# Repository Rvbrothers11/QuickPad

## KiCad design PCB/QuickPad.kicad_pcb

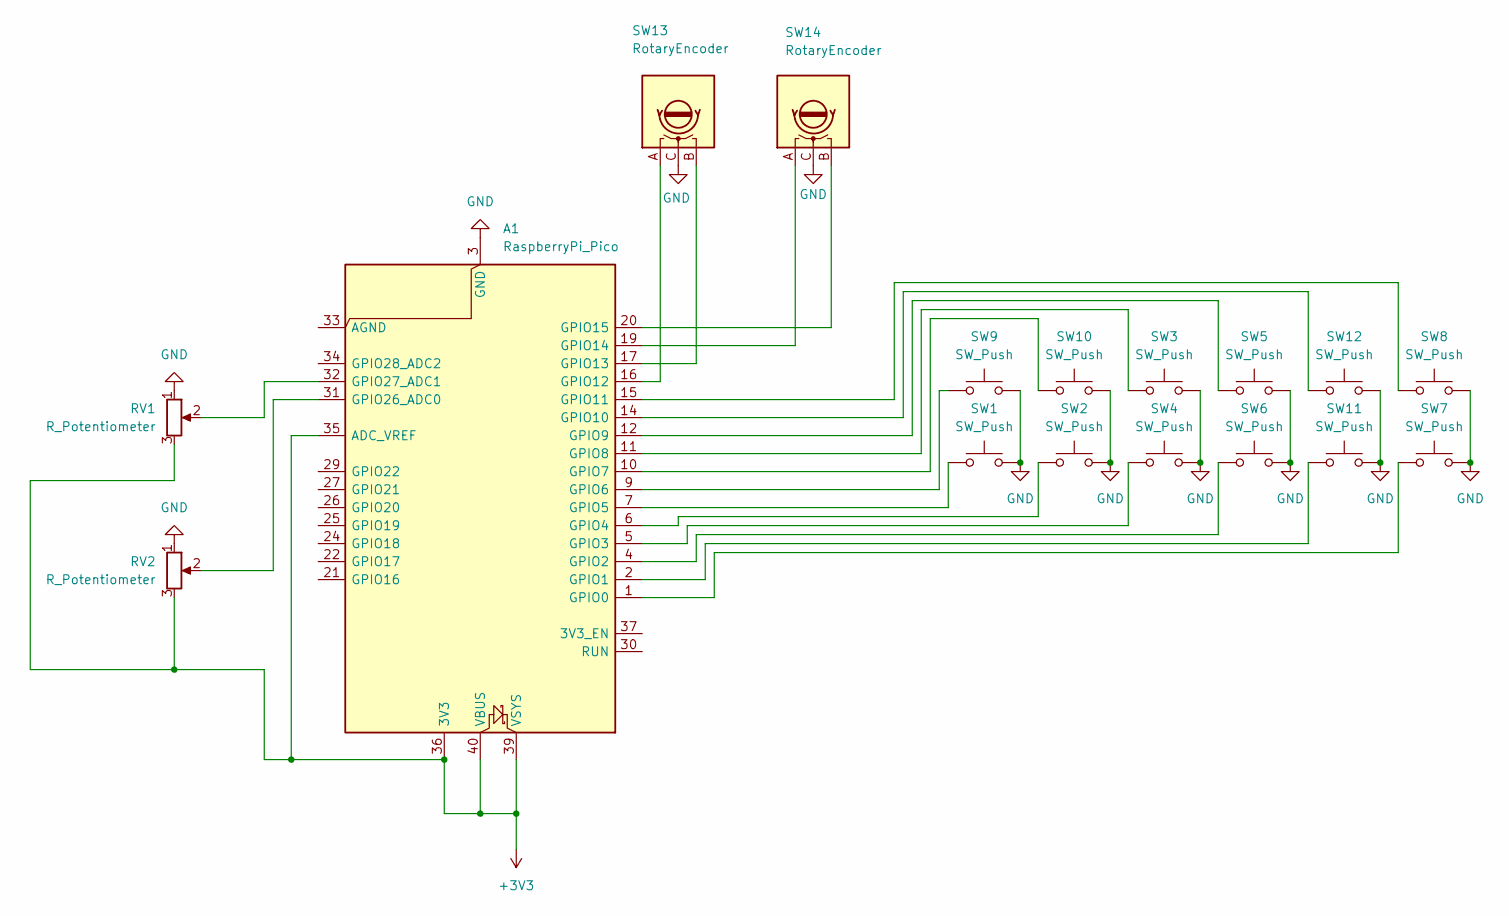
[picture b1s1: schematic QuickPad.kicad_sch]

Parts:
A1: RaspberryPi_Pico; RaspberryPi_Pico_SMD
RV1, RV2: R_Potentiometer; Potentiometer_Bourns_PTA2043_Single_Slide
SW1, SW2, SW3, SW4, SW5, SW6, SW7, SW8, SW9, SW10, SW11, SW12: SW_Push; SW_Cherry_MX_1.00u_PCB
SW13, SW14: RotaryEncoder; RotaryEncoder_Alps_EC11E-Switch_Vertical_H20mm

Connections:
+3V3: A1.35 (ADC_VREF), A1.36 (3V3), A1.39 (VSYS), A1.40 (VBUS), RV1.3, RV2.3
GND: A1.3 (GND), A1.8 (GND), A1.13 (GND), A1.18 (GND), A1.23 (GND), A1.28 (GND), A1.38 (GND), RV1.1, RV2.1, SW1.2, SW2.2, SW3.2, SW4.2, SW5.2, SW6.2, SW7.2, SW8.2, SW9.2, SW10.2, SW11.2, SW12.2, SW13.C, SW14.C
unnamed: A1.1 (GPIO0), SW7.1
unnamed: A1.2 (GPIO1), SW11.1
unnamed: A1.4 (GPIO2), SW6.1
unnamed: A1.5 (GPIO3), SW4.1
unnamed: A1.6 (GPIO4), SW2.1
unnamed: A1.7 (GPIO5), SW1.1
unnamed: A1.9 (GPIO6), SW9.1
unnamed: A1.10 (GPIO7), SW10.1
unnamed: A1.11 (GPIO8), SW3.1
unnamed: A1.12 (GPIO9), SW5.1
unnamed: A1.14 (GPIO10), SW12.1
unnamed: A1.15 (GPIO11), SW8.1
unnamed: A1.16 (GPIO12), SW13.A
unnamed: A1.17 (GPIO13), SW13.B
unnamed: A1.19 (GPIO14), SW14.A
unnamed: A1.20 (GPIO15), SW14.B
unnamed: A1.31 (GPIO26_ADC0), RV2.2
unnamed: A1.32 (GPIO27_ADC1), RV1.2

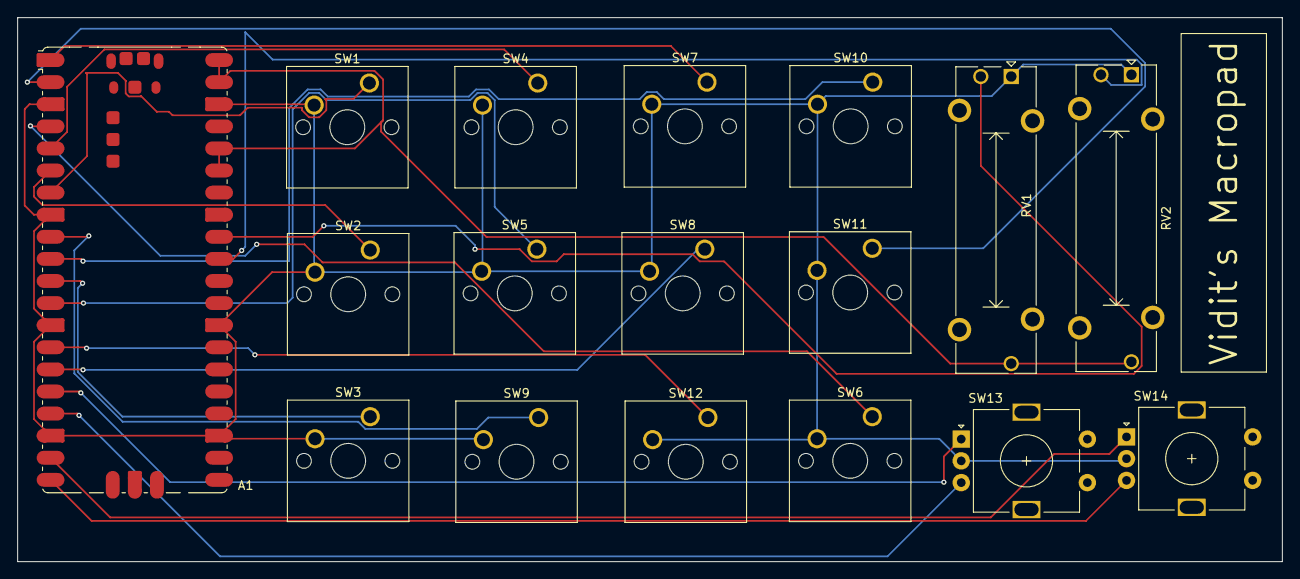
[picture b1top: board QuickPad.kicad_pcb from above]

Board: 2 copper layers, 145.4 x 62.5 mm, 17 parts (0 on the bottom side), 20 nets.

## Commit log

2026-06-06 Create a
